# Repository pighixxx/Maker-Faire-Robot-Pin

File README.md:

# Maker Faire Robot Pin

Designed for our SMD soldering workshop at Maker Faire Bilbao 2017.

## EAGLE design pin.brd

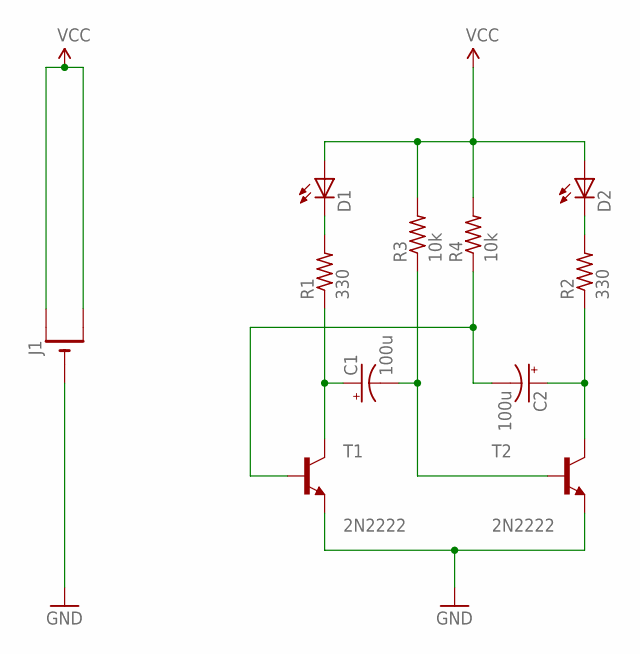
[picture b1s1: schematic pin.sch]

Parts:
C1, C2: 100u; E2-5
D1, D2: LED-3MM; LED_3MM
J1: CR1220SMT; CR1220-SMD
R1, R2: 330; 0204/5
R3, R4: 10k; 0204/5
T1, T2: 2N2222; TO92-EBC-OVAL

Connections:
CP1: C1.+, R1.1, T1.C
GND: J1.-, T1.E, T2.E
unnamed: C2.+, R2.1, T2.C
unnamed: C1.-, R3.1, T2.B
unnamed: C2.-, R4.1, T1.B
unnamed: D1.C, R1.2
unnamed: D2.C, R2.2
VCC: D1.A, D2.A, J1.+$1 (+), J1.+$2 (+1), R3.2, R4.2

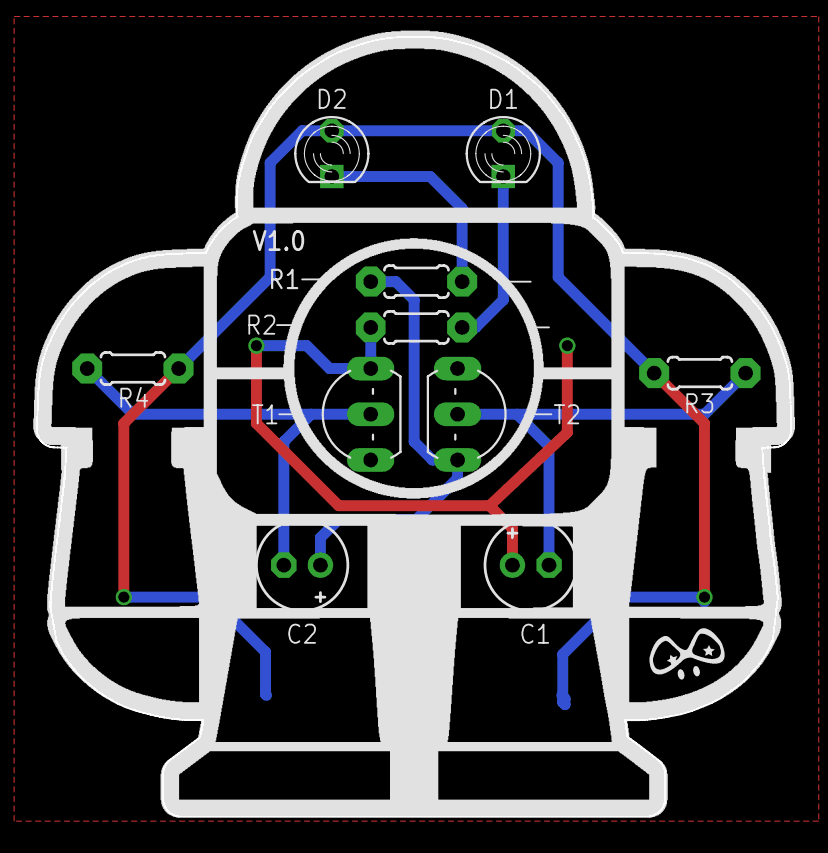
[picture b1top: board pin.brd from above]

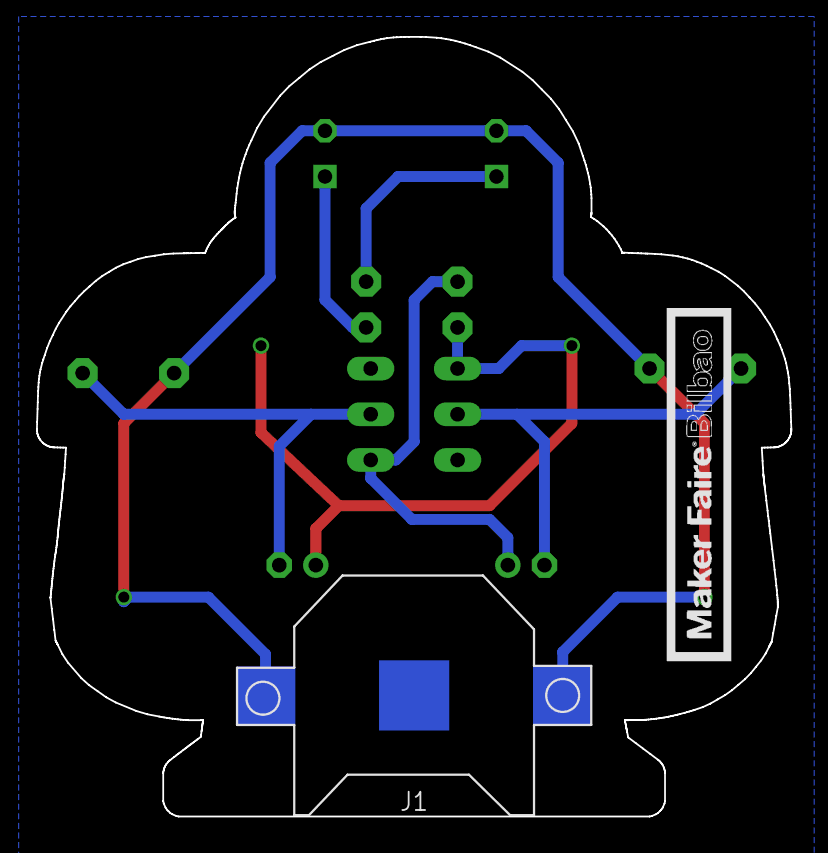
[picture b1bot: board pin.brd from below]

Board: 2 copper layers, 41.9 x 43.3 mm, 14 parts (2 on the bottom side), 8 nets.

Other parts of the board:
U$1: ROBOT2
U$3: MFBILBAO
U$5: PIGHIXXX_LOGO

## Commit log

2017-11-06 Add files
2017-11-07 Cleanup

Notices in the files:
parts and their libraries:
SparkFun-Aesthetics: Licensing: Creative Commons ShareAlike 4.0 International - https://creativecommons.org/licenses/by-sa/4.0
